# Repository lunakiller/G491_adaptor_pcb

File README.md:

# STM32G491CCUx Adaptor PCB

Adaptor PCB for STM32G491CCUx. Contains 20MHz crystal oscillator, power and user LED and separate 3.3V voltage regulators both for digital and analog part. It is possible to use only one voltage regulator or a direct 3.3V supply, in which case it is mandatory to close the SB1 solderbridge.

All free pins are routed to the edge of the board.

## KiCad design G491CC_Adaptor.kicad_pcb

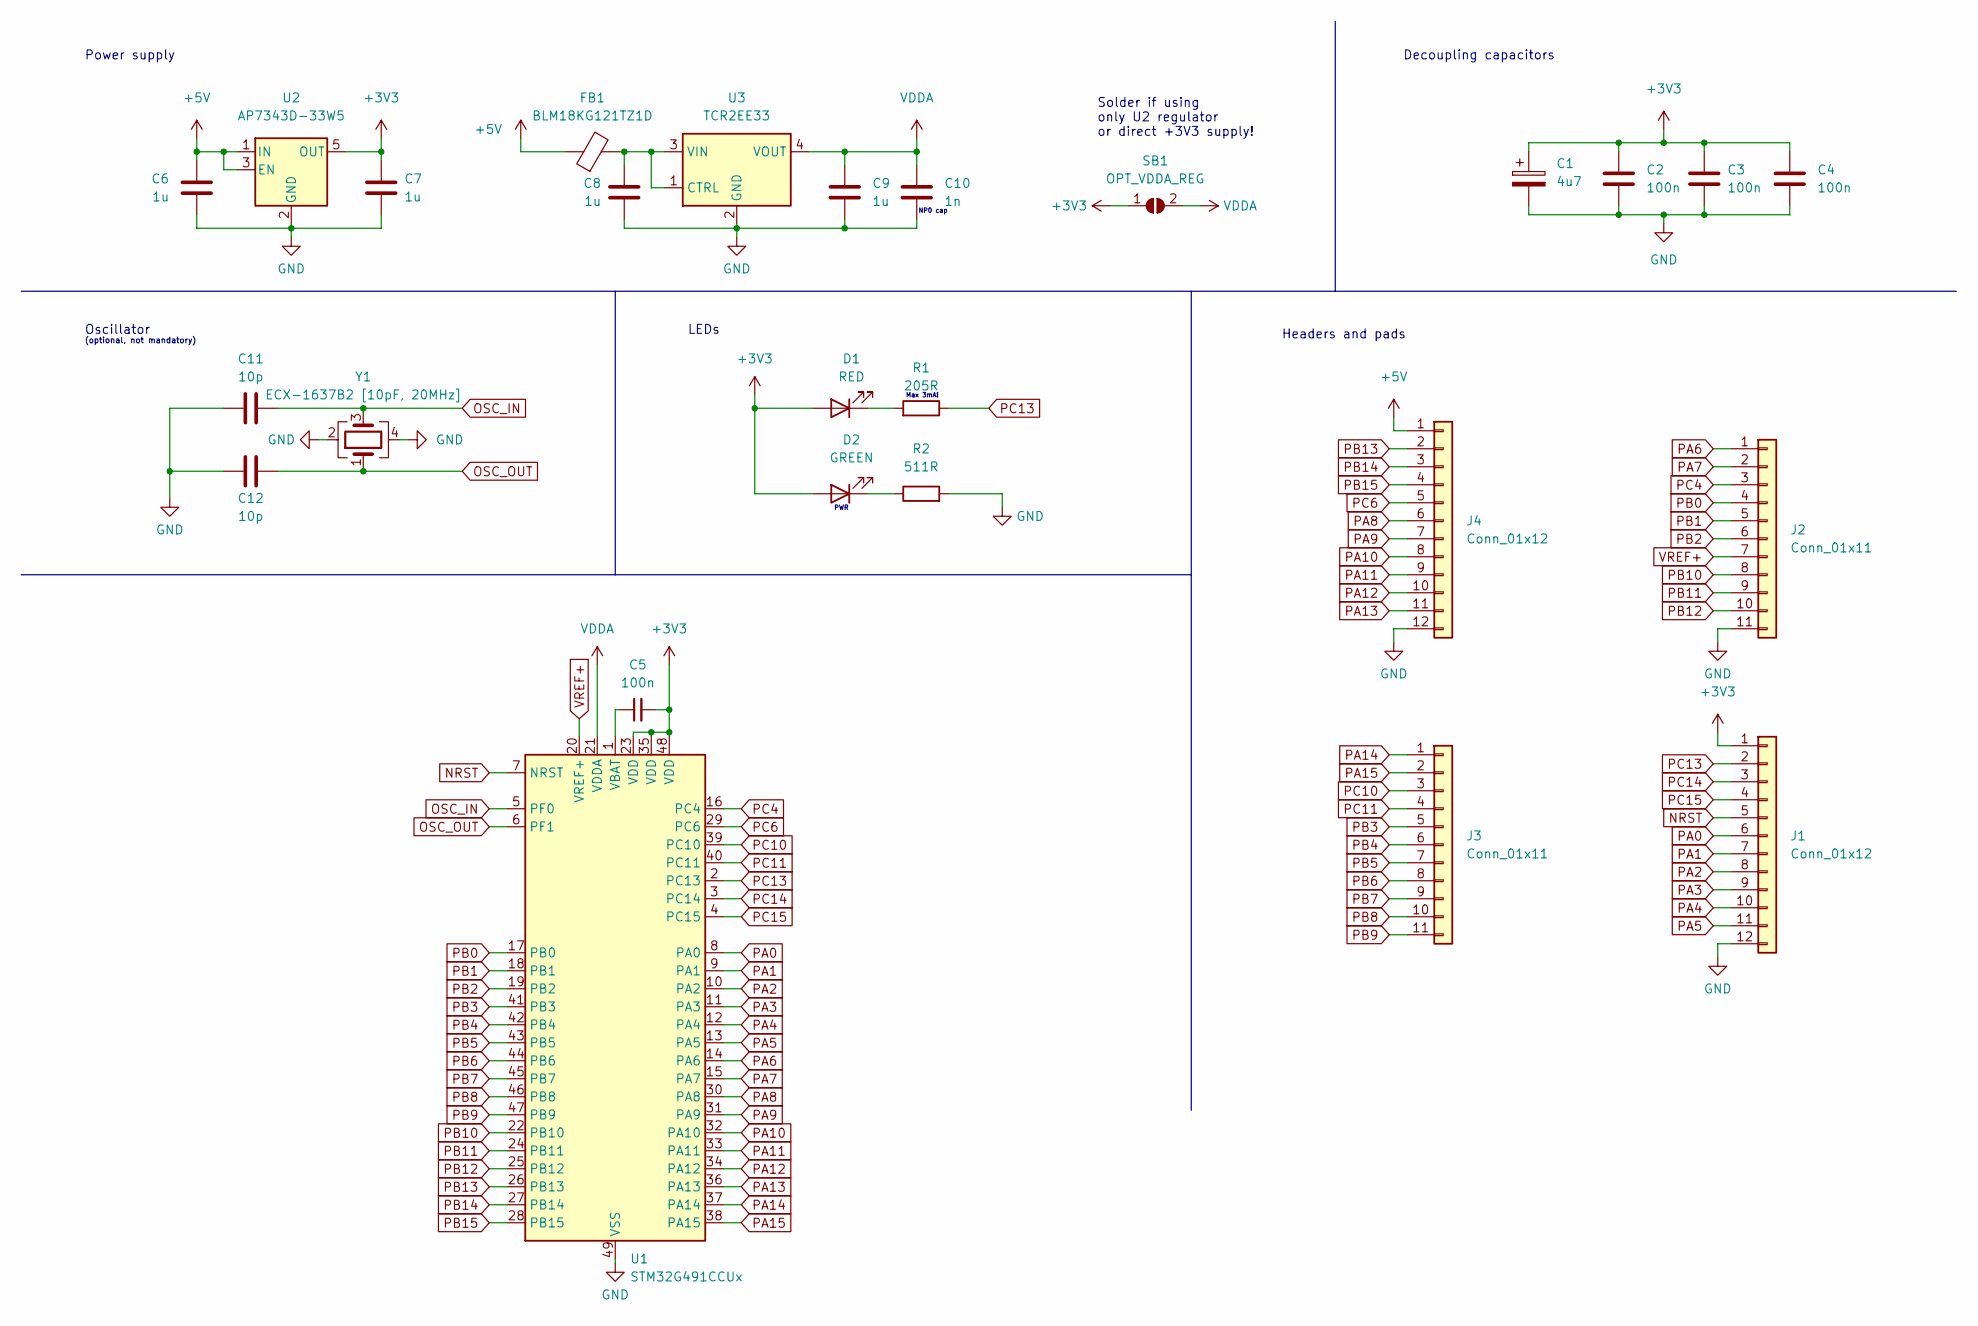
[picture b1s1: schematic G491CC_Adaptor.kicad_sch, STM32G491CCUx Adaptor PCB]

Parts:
C1: 4u7; CP_EIA-1608-10_AVX-L
C2, C3, C4, C5: 100n; C_0603_1608Metric
C6, C7, C8, C9: 1u; C_0603_1608Metric
C10: 1n; C_0603_1608Metric
C11, C12: 10p; C_0603_1608Metric
D1: RED; LED_0603_1608Metric
D2: GREEN; LED_0603_1608Metric
FB1: BLM18KG121TZ1D; L_0603_1608Metric
J1, J4: Conn_01x12; PinHeader_Castellated_1x12_P2.54mm_Vertical
J2, J3: Conn_01x11; PinHeader_Castellated_1x11_P2.54mm_Vertical
R1: 205R; R_0603_1608Metric
R2: 511R; R_0603_1608Metric
SB1: OPT_VDDA_REG; SolderJumper-2_P1.3mm_Smaller_Open_TrianglePad1.0x1.5mm
U1: STM32G491CCUx; QFN-48-1EP_7x7mm_P0.5mm_EP5.6x5.6mm
U2: AP7343D-33W5; SOT-23-5
U3: TCR2EE33; SOT-553
Y1: ECX-1637B2 [10pF, 20MHz]; Crystal_SMD_2016-4Pin_2.0x1.6mm

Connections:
+3V3: C1.1, C2.1, C3.1, C4.1, C5.2, C7.1, D1.2 (A), D2.2 (A), J1.1, SB1.1 (A), U1.23 (VDD), U1.35 (VDD), U1.48 (VDD), U2.5 (OUT)
+5V: C6.1, FB1.1, J4.1, U2.1 (IN), U2.3 (EN)
GND: C1.2, C2.2, C3.2, C4.2, C6.2, C7.2, C8.2, C9.2, C10.2, C11.1, C12.1, J1.12, J2.11, J4.12, R2.2, U1.49 (VSS), U2.2 (GND), U3.2 (GND), Y1.2, Y1.4
NRST: J1.5, U1.7 (NRST)
unnamed: C5.1, U1.1 (VBAT)
unnamed: C8.1, FB1.2, U3.1 (CTRL), U3.3 (VIN)
unnamed: D1.1 (K), R1.2
unnamed: D2.1 (K), R2.1
OSC_IN: C11.2, U1.5 (PF0), Y1.3
OSC_OUT: C12.2, U1.6 (PF1), Y1.1
PA0: J1.6, U1.8 (PA0)
PA1: J1.7, U1.9 (PA1)
PA2: J1.8, U1.10 (PA2)
PA3: J1.9, U1.11 (PA3)
PA4: J1.10, U1.12 (PA4)
PA5: J1.11, U1.13 (PA5)
PA6: J2.1, U1.14 (PA6)
PA7: J2.2, U1.15 (PA7)
PA8: J4.6, U1.30 (PA8)
PA9: J4.7, U1.31 (PA9)
PA10: J4.8, U1.32 (PA10)
PA11: J4.9, U1.33 (PA11)
PA12: J4.10, U1.34 (PA12)
PA13: J4.11, U1.36 (PA13)
PA14: J3.1, U1.37 (PA14)
PA15: J3.2, U1.38 (PA15)
PB0: J2.4, U1.17 (PB0)
PB1: J2.5, U1.18 (PB1)
PB2: J2.6, U1.19 (PB2)
PB3: J3.5, U1.41 (PB3)
PB4: J3.6, U1.42 (PB4)
PB5: J3.7, U1.43 (PB5)
PB6: J3.8, U1.44 (PB6)
PB7: J3.9, U1.45 (PB7)
PB8: J3.10, U1.46 (PB8)
PB9: J3.11, U1.47 (PB9)
PB10: J2.8, U1.22 (PB10)
PB11: J2.9, U1.24 (PB11)
PB12: J2.10, U1.25 (PB12)
PB13: J4.2, U1.26 (PB13)
PB14: J4.3, U1.27 (PB14)
PB15: J4.4, U1.28 (PB15)
PC4: J2.3, U1.16 (PC4)
PC6: J4.5, U1.29 (PC6)
PC10: J3.3, U1.39 (PC10)
PC11: J3.4, U1.40 (PC11)
PC13: J1.2, R1.1, U1.2 (PC13)
PC14: J1.3, U1.3 (PC14)
PC15: J1.4, U1.4 (PC15)
VDDA: C9.1, C10.1, SB1.2 (B), U1.21 (VDDA), U3.4 (VOUT)
VREF+: J2.7, U1.20 (VREF+)

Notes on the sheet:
PWR
NP0 cap
Oscillator
Max 3mA!
LEDs
Headers and pads
Decoupling capacitors
Solder if using only U2 regulator or direct +3V3 supply!
(optional, not mandatory)
Power supply

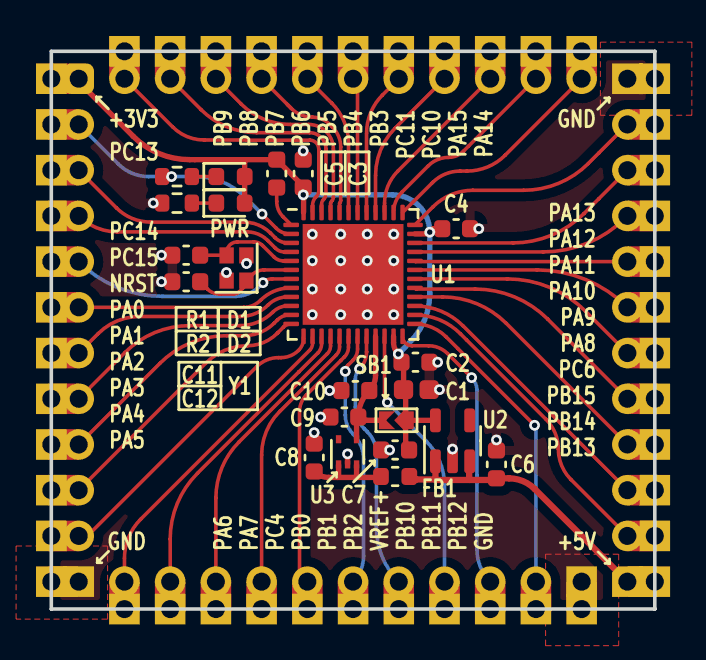
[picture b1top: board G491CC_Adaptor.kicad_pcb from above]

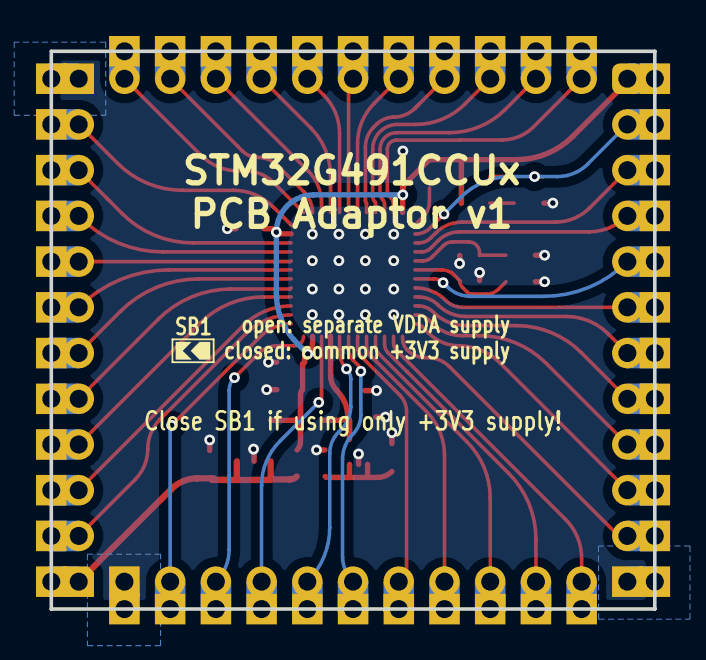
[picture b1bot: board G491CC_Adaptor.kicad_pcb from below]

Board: 2 copper layers, 33.5 x 31.0 mm, 26 parts (4 on the bottom side), 51 nets.

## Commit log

2022-07-27 Upload files
2022-07-27 Added LICENSE
2022-08-17 LED resistor values
